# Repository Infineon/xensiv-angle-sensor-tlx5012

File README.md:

# XENSIV™ TLx5012B Angle Sensor

Library of Infineon's highly sensitive [XENSIV™ TLx5012B](https://www.infineon.com/products/sensor/magnetic-position-sensors/angle-sensors) 360° magnetic angle sensor.

### Suported Products

|  |  |  |
|:--:|:--:|:--:|
| *bulk sensor* | *breakout board* | *Sensor2Go kit* 

This library supports also all predefined communication variants IIF, PWM, SPC. All of these variants also support the SSC interface.

### Supported Frameworks

<table>
    <tr>
        <td></td>
        <td></td>
    </tr>
    <tr>
        <td style="text-align: center"><a href="https://github.com/Infineon/TLE5012-Magnetic-Angle-Sensor/wiki/Arduino-API">Arduino API</a></td>
        <td style="text-align: center"><a href="https://github.com/Infineon/TLE5012-Magnetic-Angle-Sensor/wiki/TLE5012B-API/">TLE5012B API</a><br><a href="https://github.com/Infineon/TLE5012-Magnetic-Angle-Sensor/wiki/TLE5012BMotor-API">TLx5012B Register API</a></td>
    </tr>
    <tr>
        <td style="text-align: center"><a href="https://github.com/Infineon/TLE5012-Magnetic-Angle-Sensor/wiki/Ino-Getting-Started">Getting Started</a></td>
        <td style="text-align: center"><a href="https://github.com/Infineon/TLE5012-Magnetic-Angle-Sensor/wiki/Porting-Guide">Porting Guide</a></td>
    </tr>
</table>

## Summary
The [TLE5012B](https://www.infineon.com/cms/en/product/evaluation-boards/tle5012b_e1000_ms2go/) is a 360° angle sensor that detects the orientation of a magnetic field. This is achieved by measuring sine and cosine angle components with monolithic integrated Giant Magneto Resistance (iGMR) elements. These raw signals (sine and cosine) are digitally processed internally to calculate the angle orientation of the magnetic field (magnet). The TLx5012B is a pre-calibrated sensor. The calibration parameters are stored in laser fuses. At start-up the values of the fuses are written into flip-flops, where these values can be changed by the application-specific parameters. Further precision of the angle measurement over a wide temperature range and a long lifetime can be improved by enabling an optional internal auto calibration algorithm. Data communications are accomplished with a bi-directional Synchronous Serial Communication (SSC) that is SPI-compatible. The sensor configuration is stored in registers, which are accessible by the SSC interface. Additionally four other interfaces are available with the TLx5012B: Pulse-Width-Modulation (PWM) Protocol, Short-PWM-Code (SPC) Protocol, Hall Switch Mode (HSM) and Incremental Interface (IIF). These interfaces can be used in parallel with SSC or alone. Pre-configured sensor derivate with different interface settings are available.

## Key Features and Benefits
* Giant Magneto Resistance (GMR)-based principle
* Integrated magnetic field sensing for angle measurement
* 360° angle measurement with revolution counter and angle speed measurement
* Two separate highly accurate single bit SD-ADC
* 15 bit representation of absolute angle value on the output (resolution of 0.01°)
* 16 bit representation of sine / cosine values on the interface
* Max. 1.0° angle error over lifetime and temperature-range with activated auto-calibration
* Bi-directional SSC Interface up to 8 Mbit/s
* Interfaces: SSC, PWM, Incremental Interface (IIF), Hall Switch Mode (HSM), Short PWM Code (SPC, based on SENT protocol defined in SAE J2716)
* Output pins can be configured (programmed or pre-configured) as push-pull or open-drain
* Bus mode operation of multiple sensors on one line is possible with SSC or SPC interface

## More information
The complete documentation of the library as well as detailed information about the XENSIV™ TLx5012B Angle Sensor, can be found [here](https://xensiv-angle-sensor-tlx5012.readthedocs.io/en/latest/index.html).

## License

This project is licensed under the MIT License - see the [LICENSE](LICENSE) file for details.

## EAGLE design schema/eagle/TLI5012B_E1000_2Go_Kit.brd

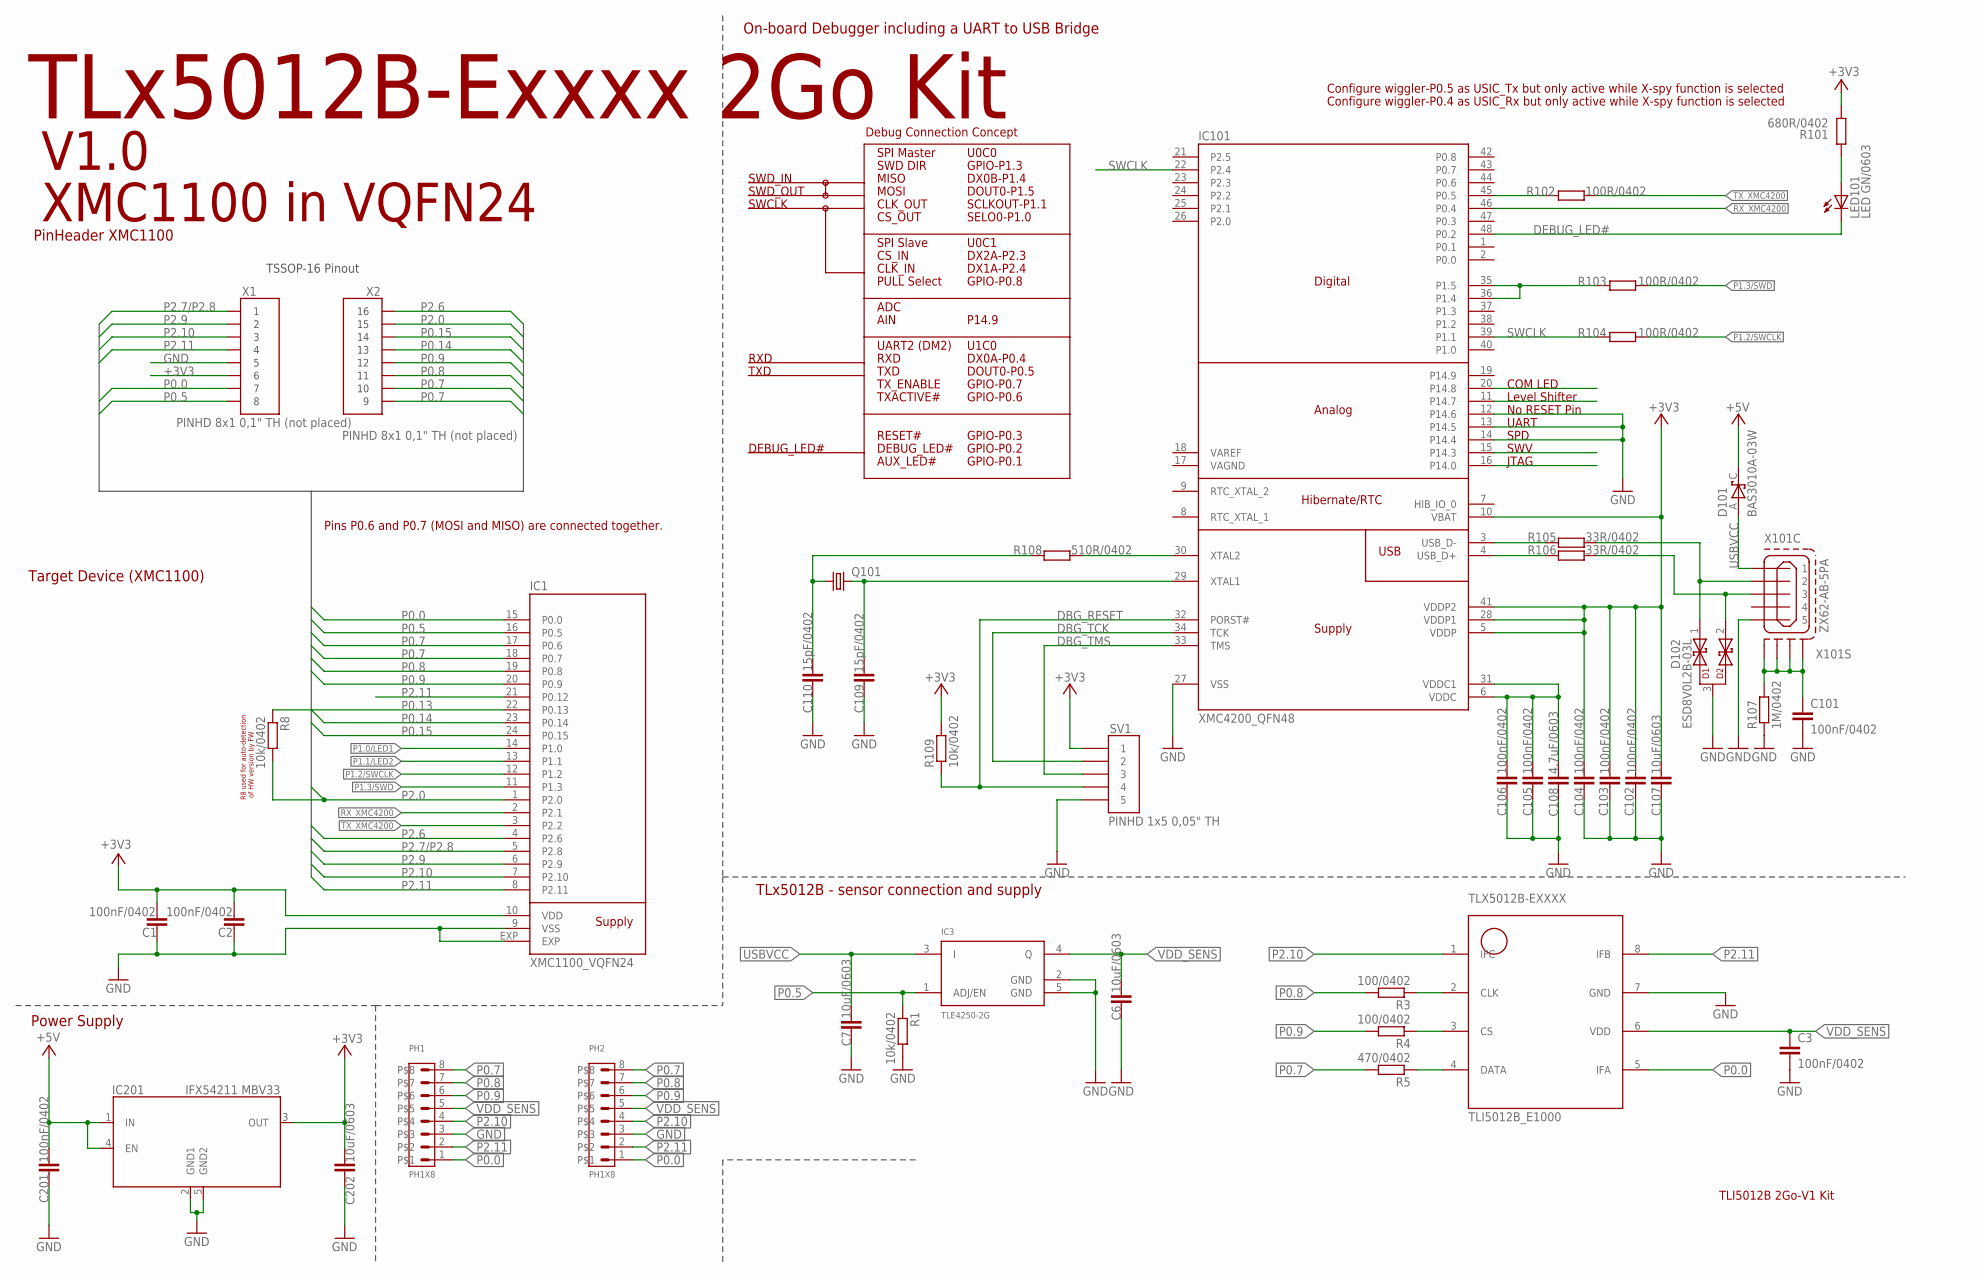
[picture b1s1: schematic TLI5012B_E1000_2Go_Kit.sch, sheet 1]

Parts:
C1, C2, C3, C101, C102, C103, C104, C105, C106, C201: 100nF/0402; C0402
C6, C7, C107, C202: 10uF/0603; C0603
C108: 4,7uF/0603; C0603
C109, C110: 15pF/0402; C0402
D101: BAS3010A-03W; SOD323-R
D102: ESD8V0L2B-03L; TSLP-3-1
IC1: XMC1100_VQFN24; VQFN24
IC3: TLE4250-2G; PG-SCT595
IC101: XMC4200_QFN48; QFN-48-7X7
IC201: IFX54211 MBV33; SCT595_INFINEON
LED101: LED GN/0603; CHIPLED_0603
PH1, PH2: PH1X8; PH005-1-8
Q101: NX3225_2; 32X25_4PAD
R1, R8, R109: 10k/0402; R0402
R3, R4: 100/0402; R0402
R5: 470/0402; R0402
R101: 680R/0402; R0402
R102, R103, R104: 100R/0402; R0402
R105, R106: 33R/0402; R0402
R107: 1M/0402; R0402
R108: 510R/0402; R0402
SV1: PINHD 1x5 0,05" TH; PINHEAD_127
TLX5012B-EXXXX: TLI5012B_E1000; INF-PG-DSO-8-16
X1, X2: PINHD 8x1 0,1" TH (not placed); PINHD_1X8_SP
X101: ZX62-AB-5PA; ZX62-AB-5PA_MICRO-USB

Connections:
+3V3: C1.2, C2.2, C102.1, C103.1, C104.1, C107.1, C202.1, IC1.10 (VDD), IC101.5 (VDDP), IC101.10 (VBAT), IC101.28 (VDDP1), IC101.41 (VDDP2), IC201.3 (OUT), R101.1, R109.2, SV1.P$1 (1), X1.6
+5V: C201.1, D101.C, IC201.1 (IN), IC201.4 (EN)
DBG_RESET: IC101.32 (PORST#), R109.1, SV1.P$4 (4)
DBG_TCK: IC101.34 (TCK), SV1.P$2 (2)
DBG_TMS: IC101.33 (TMS), SV1.P$3 (3)
DEBUG_LED#: IC101.48 (P0.2), LED101.C
GND: C1.1, C2.1, C3.2, C6.2, C7.2, C101.2, C102.2, C103.2, C104.2, C105.2, C106.2, C107.2, C108.2, C109.2, C110.2, C201.2, C202.2, D102.3, IC1.9 (VSS), IC1.EXP, IC3.2 (GND), IC3.5 (GND), IC101.12 (P14.6), IC101.13 (P14.5), IC101.14 (P14.4), IC101.27 (VSS), IC201.2 (GND1), IC201.5 (GND2), PH1.3, PH2.3, R1.2, R107.1, SV1.P$5 (5), TLX5012B-EXXXX.7 (GND), X1.5, X101.5; also elsewhere on the board
unnamed: IC101.35 (P1.5), IC101.36 (P1.4), R103.1
unnamed: R3.1, TLX5012B-EXXXX.2 (CLK)
unnamed: R4.1, TLX5012B-EXXXX.3 (CS)
unnamed: IC101.45 (P0.5), R102.1
unnamed: R5.1, TLX5012B-EXXXX.4 (DATA)
unnamed: C101.1, R107.2, X101.S1, X101.S2, X101.S3, X101.S4
unnamed: LED101.A, R101.2
unnamed: D102.1, R105.2, X101.2
unnamed: D102.2, R106.2, X101.3
unnamed: IC101.30 (XTAL2), R108.2
unnamed: C110.1, Q101.1, R108.1
P0.0: IC1.15 (P0.0), PH1.1, PH2.1, TLX5012B-EXXXX.5 (IFA), X1.7; also elsewhere on the board
P0.5: IC1.16 (P0.5), IC3.1 (ADJ/EN), R1.1, X1.8
P0.7: IC1.17 (P0.6), IC1.18 (P0.7), PH1.8, PH2.8, R5.2, X2.7, X2.8
P0.8: IC1.19 (P0.8), PH1.7, PH2.7, R3.2, X2.6
P0.9: IC1.20 (P0.9), PH1.6, PH2.6, R4.2, X2.5
P0.13: IC1.22 (P0.13), R8.1
P0.14: IC1.23 (P0.14), X2.4; also elsewhere on the board
P0.15: IC1.24 (P0.15), X2.3; also elsewhere on the board
P1.0/LED1: IC1.14 (P1.0)
P1.1/LED2: IC1.13 (P1.1)
P1.2/SWCLK: IC1.12 (P1.2), R104.2
P1.3/SWD: IC1.11 (P1.3), R103.2
P2.0: IC1.1 (P2.0), R8.2, X2.2
P2.6: IC1.4 (P2.6), X2.1
P2.7/P2.8: IC1.5 (P2.8), X1.P$1
P2.9: IC1.6 (P2.9), X1.2
P2.10: IC1.7 (P2.10), PH1.4, PH2.4, TLX5012B-EXXXX.1 (IFC), X1.3
P2.11: IC1.8 (P2.11), IC1.21 (P0.12), PH1.2, PH2.2, TLX5012B-EXXXX.8 (IFB), X1.4
Q200: C109.1, IC101.29 (XTAL1), Q101.3 (2)
RX_XMC4200: IC1.2 (P2.1), IC101.46 (P0.4)
SWCLK: IC101.22 (P2.4), IC101.39 (P1.1), R104.1
TX_XMC4200: IC1.3 (P2.2), R102.2
USBVCC: C7.1, D101.A, IC3.3 (I), X101.1
VDD_SENS: C3.1, C6.1, IC3.4 (Q), PH1.5, PH2.5, TLX5012B-EXXXX.6 (VDD); also elsewhere on the board
WUSB_DM: IC101.3 (USB_D-), R105.1
WUSB_DP: IC101.4 (USB_D+), R106.1
WVDDC: C105.1, C106.1, C108.1, IC101.6 (VDDC), IC101.31 (VDDC1)

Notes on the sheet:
TLI5012B 2Go-V1 Kit
On-board Debugger including a UART to USB Bridge
Configure wiggler-P0.5 as USIC_Tx but only active while X-spy function is selected
Configure wiggler-P0.4 as USIC_Rx but only active while X-spy function is selected
SCLKOUT-P1.1
DX0B-P1.4
SPI Slave
SWD_OUT
SWCLK
MOSI
CLK_OUT
MISO
CS_IN
CLK_IN
CS_OUT
SPI Master
U0C0
U0C1
DOUT0-P1.5
SELO0-P1.0
DX2A-P2.3
DX1A-P2.4
RXD
TXD
UART2 (DM2)
DX0A-P0.4
DOUT0-P0.5
U1C0
TXACTIVE#
GPIO-P0.6
RESET#
GPIO-P0.3
DEBUG_LED#
GPIO-P0.2
TX_ENABLE
GPIO-P0.7
SWD DIR
GPIO-P1.3
SWD_IN
ADC

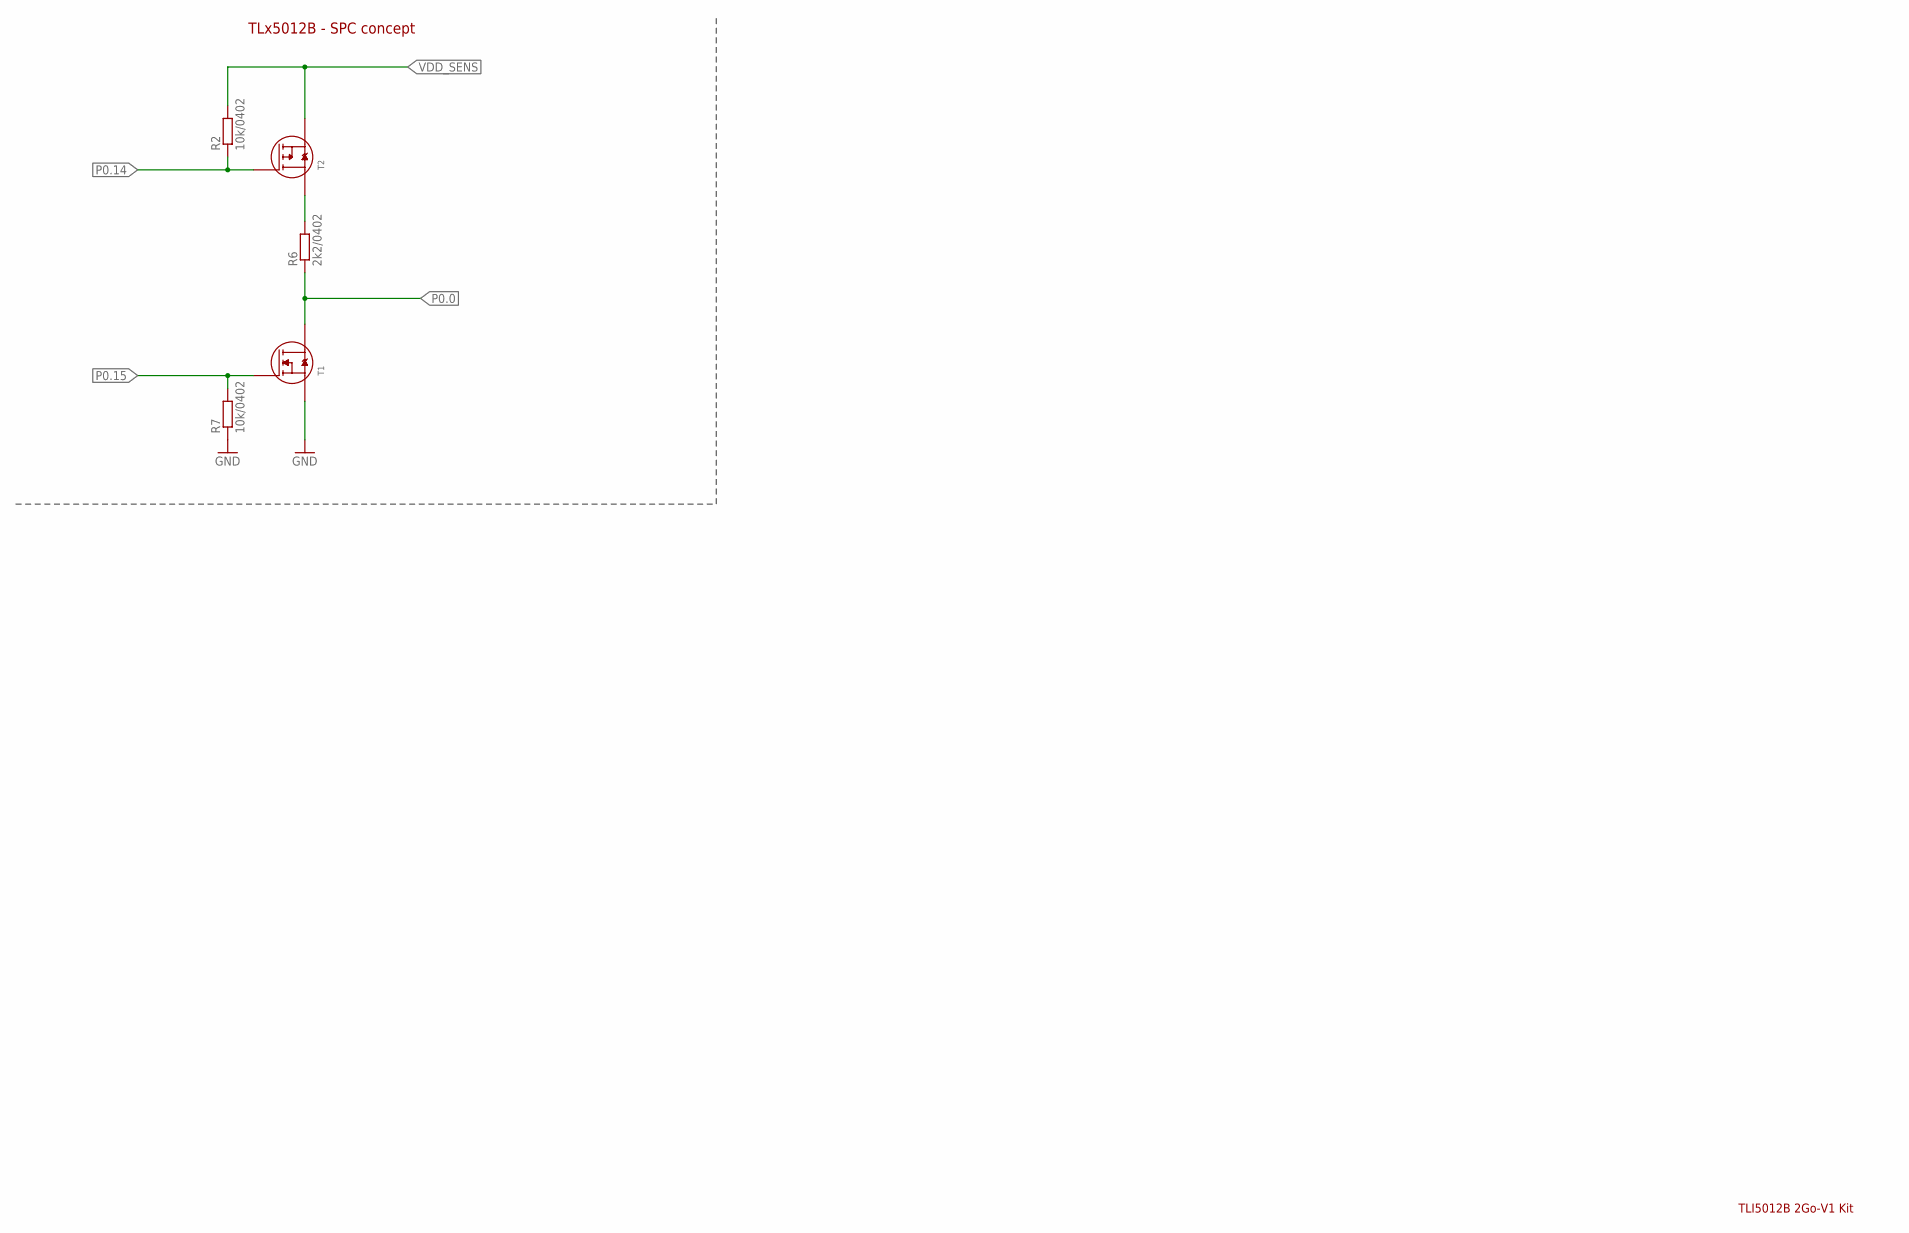
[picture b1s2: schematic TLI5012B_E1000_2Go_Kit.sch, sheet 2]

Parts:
R2, R7: 10k/0402; R0402
R6: 2k2/0402; R0402
T1: BSS138N; INF-PG-SOT23_N_1PRIMARY
T2: BSS84P; INF-PG-SOT23_N_1PRIMARY

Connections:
GND: R7.1, T1.2 (S); also elsewhere on the board
unnamed: R6.2, T2.3 (D)
P0.0: R6.1, T1.3 (D); also elsewhere on the board
P0.14: R2.1, T2.1 (G); also elsewhere on the board
P0.15: R7.2, T1.1 (G); also elsewhere on the board
VDD_SENS: R2.2, T2.2 (S); also elsewhere on the board

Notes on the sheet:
TLI5012B 2Go-V1 Kit
TLx5012B - SPC concept

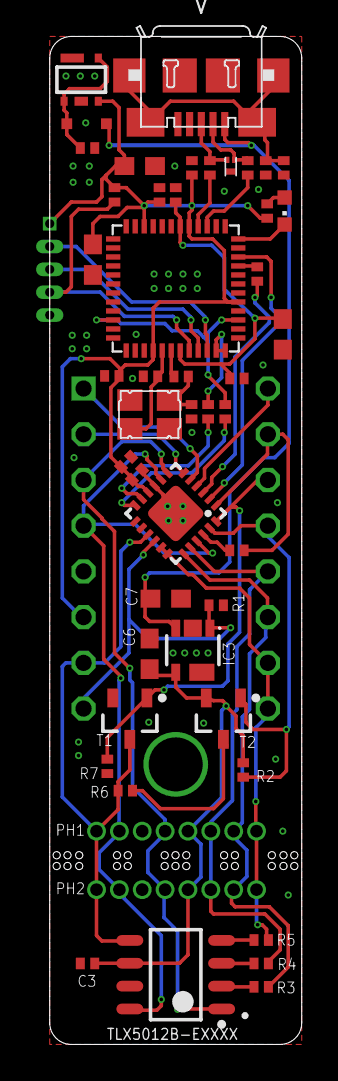
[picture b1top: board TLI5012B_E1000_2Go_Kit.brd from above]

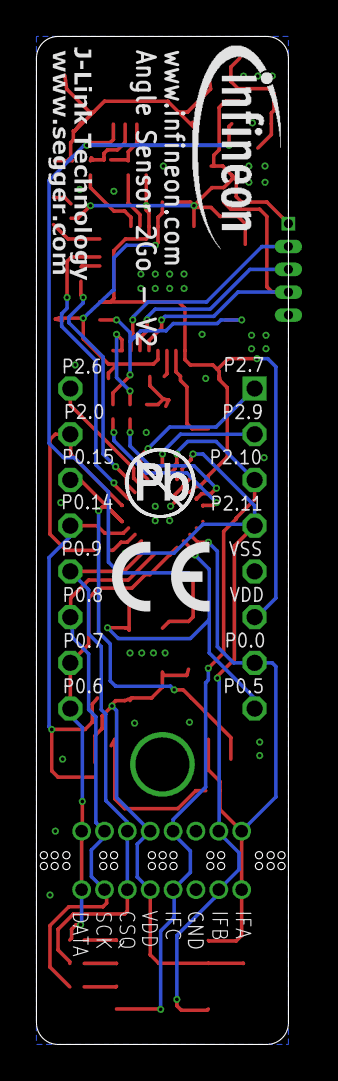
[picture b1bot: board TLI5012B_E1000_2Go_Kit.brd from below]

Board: 2 copper layers, 14.0 x 56.0 mm, 53 parts (2 on the bottom side), 44 nets.

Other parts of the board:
U$2: INFINEON_LOGO_INFINEON_LOGO_5_SILK
U$3: CE_KENNEZCIHNUNG

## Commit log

2024-10-18 Initial insertation for new TLx5012B library
2024-10-21 Use a parameter for timeout
2024-10-22 Fix bug in link setting
2024-10-22 Add runtime keyword
2024-10-23 Parametric arduino version test
2025-03-07 New ReadTheDocs documentation
2025-03-07 Bugfixing and testing of many different MCU boards
2025-03-07 Insert github action and internal workflow
2025-03-07 Upgrade main text files
2025-03-07 Insert schema files for fritzing, eagle, altium'
2025-03-07 docs: Prepare publication on ReadTheDocs
2025-05-23 Changes from customer input, change formatting
2025-07-04 add docs check
2025-09-19 link_repair
2025-09-19 href correction
2025-09-19 correction Licence link
2025-09-19 link repair
2025-11-13 Add link checks & replace broken links.
    * link_repair
    * href correction
    * correction Licence link
    * link repair
2026-02-05 src/framework/arduino/pal: Updated XMC architecture.
2026-02-06 .github: Update xmc version.
2026-02-06 .github: Updated FQBN name.
2026-02-06 src/framework/arduino: Updated FQBN name in arduino examples.
2026-02-06 src/framework/arduino: Modified FQBN name.
2026-02-06 src/framework/arduino/pal: Updated class name.
2026-02-06 .github: Modified latest version names.
2026-02-06 platformio: Revert board name to old.
2026-02-06 .github: Modified platformio board name.
2026-02-06 src/framework/arduino: Dummy commit.
2026-02-06 src/framework: Dummy commit.
2026-03-02 Update TLE5012B_UM_V01_02_EN
2026-03-02 Fix LICENSE-links and update URLs
2026-05-08 CODEOWNERS: Add code owners.
2026-05-08 CODE_OF_CONDUCT.md: Add Code of Conduct.
